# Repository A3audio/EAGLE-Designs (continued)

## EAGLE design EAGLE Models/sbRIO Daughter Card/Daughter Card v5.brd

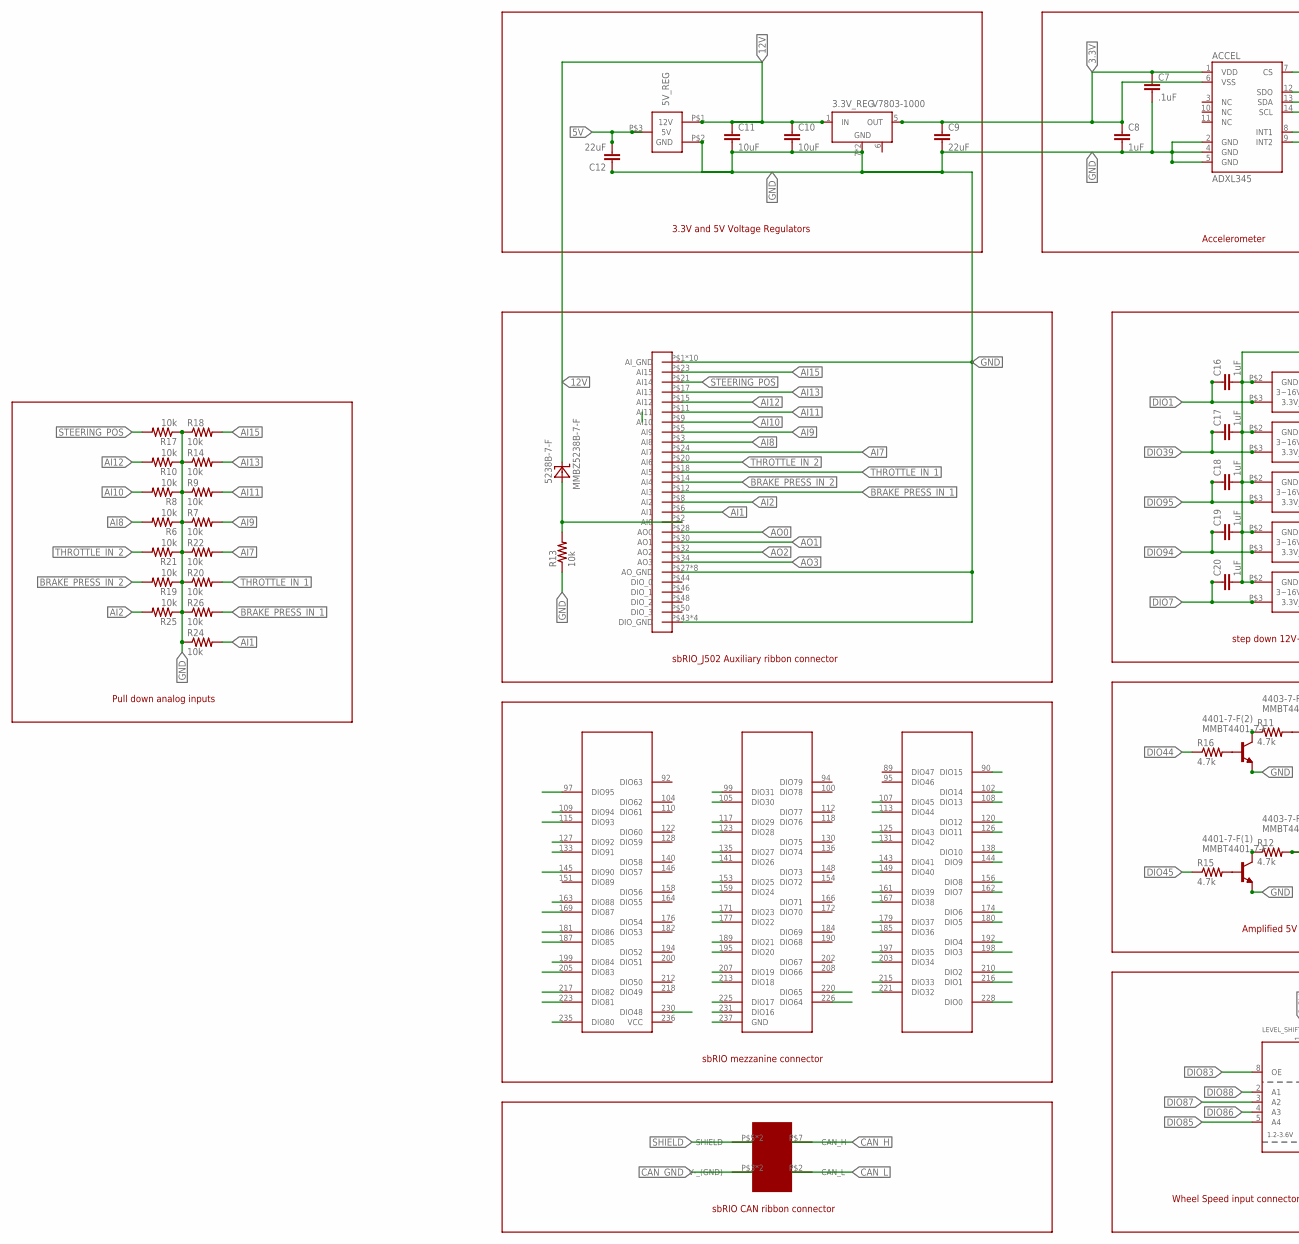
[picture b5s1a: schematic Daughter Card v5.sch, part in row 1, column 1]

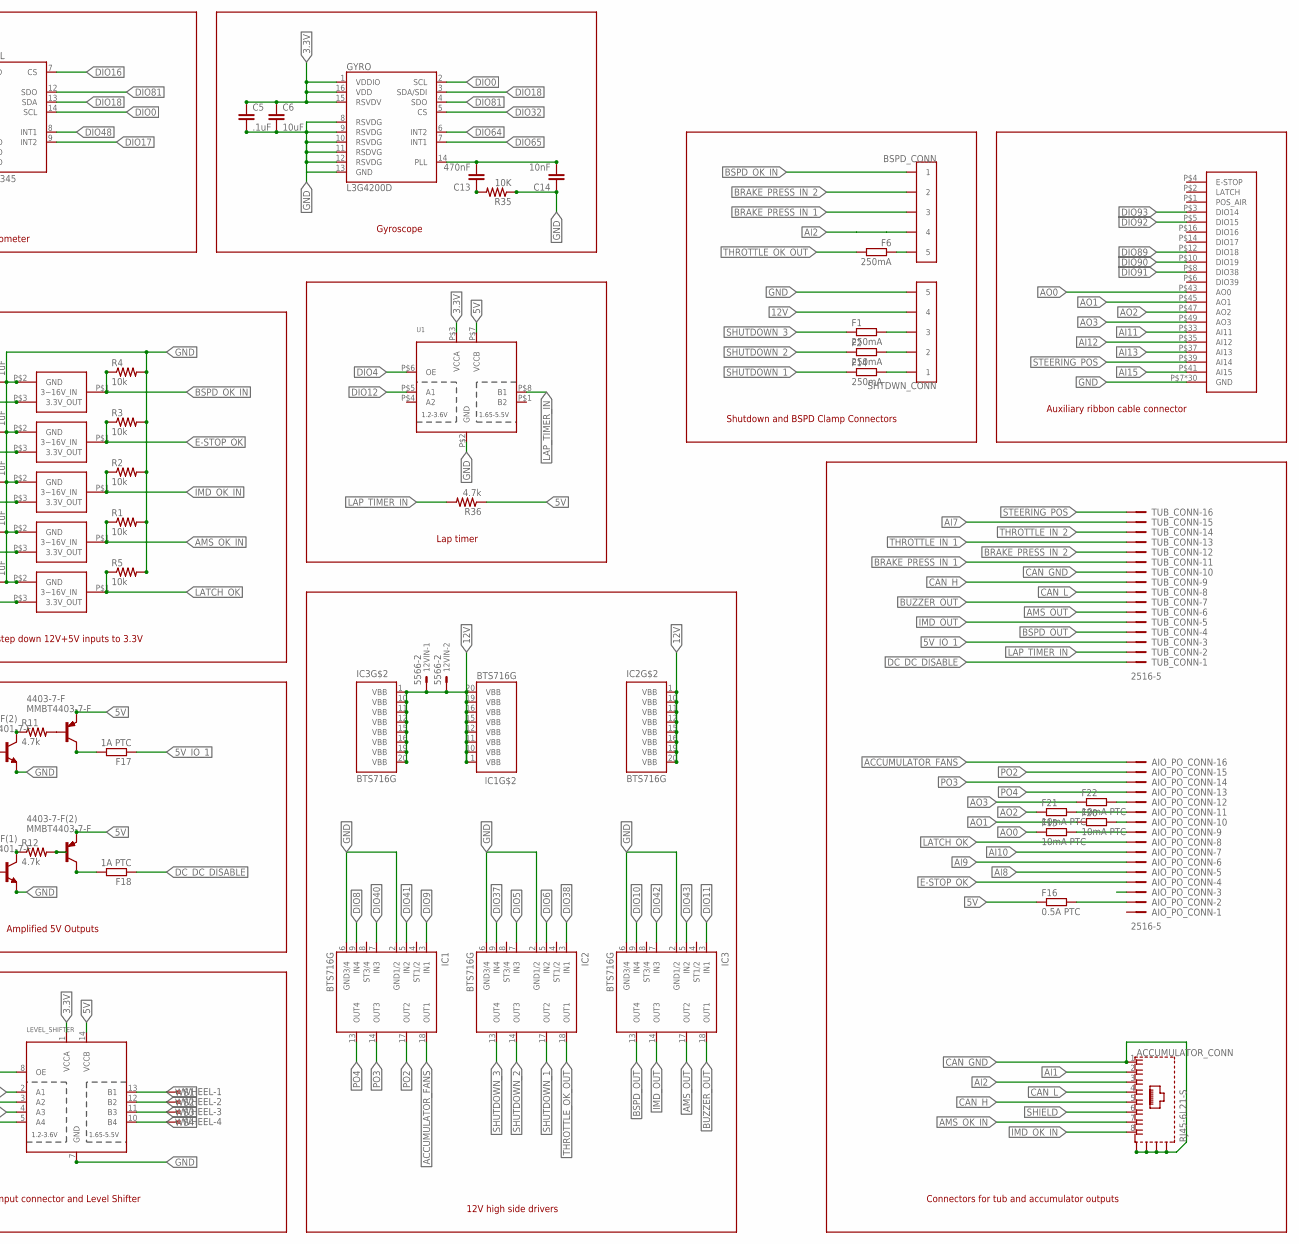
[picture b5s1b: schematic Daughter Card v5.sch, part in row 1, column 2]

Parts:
3.3V_REG: V7803-1000; V78XX-1000
5V_REG: V78XX-1500; V78XX-1500R
12VIN: 5566-2
4401-7-F(1), 4401-7-F(2): MMBT4401-7-F; SOT-23-3
4403-7-F, 4403-7-F(2): MMBT4403-7-F; SOT-23-3
5225-3.3M5-TR(5), 5525-3.3YM5-TR(1), 5525-3.3YM5-TR(2), 5525-3.3YM5-TR(3), 5525-3.3YM5-TR(4): MIC5225-3.3YM5-TR; SOT-23-3
5238B-7-F: MMBZ5238B-7-F; SOT-23-3
ACCEL: ADXL345; LGA14
ACCUMULATOR_CONN: RJ45-6L21-S; RJ45-SHIELD1
AIO_PO_CONN: 2516-5; PAK100/2500-5-16
BSPD_CONN: CONN_5; CONNECTOR_5
C5, C7: .1uF; 0603-CAP
C6, C10, C11: 10uF; 0603-CAP
C8, C16, C17, C18, C19, C20: 1uF; 0603-CAP
C9, C12: 22uF; 0603-CAP
C13: 470nF; 0603-CAP
C14: 10nF; 0603-CAP
F1, F2, F6, F14: 250mA; R0603
F15, F20, F21, F22: 10mA PTC; R0402
F16: 0.5A PTC; R0603
F17, F18: 1A PTC; R0603
GYRO: L3G4200D; LGA16-4X4
IC1, IC2, IC3: BTS716G; PG-DSO-20
LEVEL_SHIFTER: TXB0104PWR; TSSOP14
R1, R2, R3, R4, R5, R6, R7, R8, R9, R10, R13, R14, R17, R18, R19, R20, R21, R22, R24, R25, R26: 10k; R0402
R11, R12, R15, R16, R36: 4.7k; R0402
R35: 10K; 0603-RES
SBRIO_ANALOG: SBRIO_MIO; SBRIO_J502_J503
SBRIO_AUX: SBRIO_AUX; SBRIO_J502_J503
SBRIO_CAN: SBRIO_W500; SBRIO_W
SBRIO_MEZZANINE: SBRIO_RMC; SEAM-40-XX.X-XX-06-X-A
SHTDWN_CONN: CONN_5; CONNECTOR_5
TUB_CONN: 2516-5; PAK100/2500-5-16
U1: TXS0102; VFSOP-8
WHEEL: FTOP-4

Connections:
3.3V: 3.3V_REG.5 (OUT), ACCEL.1 (VDD), ACCEL.6 (VSS), C5.1, C6.1, C7.1, C8.1, C9.1, GYRO.1 (VDDIO), GYRO.15 (RSVDV), GYRO.16 (VDD), LEVEL_SHIFTER.1 (VCCA), U1.P$3 (VCCA)
5V: 5V_REG.P$3 (5V), 4403-7-F.P$3 (E), 4403-7-F(2).P$3 (E), C12.2, F16.1, LEVEL_SHIFTER.14 (VCCB), R36.1, U1.P$7 (VCCB)
5V_FUSED: AIO_PO_CONN.2, F16.2
5V_IO_1: F17.1, TUB_CONN.3
12V: 3.3V_REG.1 (IN), 5V_REG.P$1 (12V), 12VIN.1, 12VIN.2, 5238B-7-F.P$1 (C), C10.1, C11.1, IC1.1 (VBB), IC1.10 (VBB), IC1.11 (VBB), IC1.12 (VBB), IC1.15 (VBB), IC1.16 (VBB), IC1.19 (VBB), IC1.20 (VBB), IC2.1 (VBB), IC2.10 (VBB), IC2.11 (VBB), IC2.12 (VBB), IC2.15 (VBB), IC2.16 (VBB), IC2.19 (VBB), IC2.20 (VBB), IC3.1 (VBB), IC3.10 (VBB), IC3.11 (VBB), IC3.12 (VBB), IC3.15 (VBB), IC3.16 (VBB), IC3.19 (VBB), IC3.20 (VBB), SHTDWN_CONN.7 (4), SHTDWN_CONN.8 (4)
ACCUMULATOR_FANS: AIO_PO_CONN.16, IC1.18 (OUT1)
AI1: ACCUMULATOR_CONN.2, R24.2, SBRIO_ANALOG.P$6 (AI1)
AI2: ACCUMULATOR_CONN.3, BSPD_CONN.7 (4), BSPD_CONN.8 (4), R25.2, SBRIO_ANALOG.P$8 (AI2)
AI7: R22.2, SBRIO_ANALOG.P$24 (AI7), TUB_CONN.15
AI8: AIO_PO_CONN.5, R6.2, SBRIO_ANALOG.P$3 (AI8)
AI9: AIO_PO_CONN.6, R7.2, SBRIO_ANALOG.P$5 (AI9)
AI10: AIO_PO_CONN.7, R8.2, SBRIO_ANALOG.P$9 (AI10)
AI11: R9.2, SBRIO_ANALOG.P$11 (AI11), SBRIO_AUX.P$33 (AI11)
AI12: R10.2, SBRIO_ANALOG.P$15 (AI12), SBRIO_AUX.P$35 (AI12)
AI13: R14.2, SBRIO_ANALOG.P$17 (AI13), SBRIO_AUX.P$37 (AI13)
AI15: R18.2, SBRIO_ANALOG.P$23 (AI15), SBRIO_AUX.P$41 (AI15)
AMS_OK_IN: 5525-3.3YM5-TR(1).P$1 (3~16V_IN), ACCUMULATOR_CONN.7, R1.1
AMS_OUT: IC3.17 (OUT2), TUB_CONN.6
AO0: F15.1, SBRIO_ANALOG.P$28 (AO0), SBRIO_AUX.P$43 (AO0)
AO1: F20.1, SBRIO_ANALOG.P$30 (AO1), SBRIO_AUX.P$45 (AO1)
AO2: F21.1, SBRIO_ANALOG.P$32 (AO2), SBRIO_AUX.P$47 (AO2)
AO3: F22.1, SBRIO_ANALOG.P$34 (AO3), SBRIO_AUX.P$49 (AO3)
BRAKE_PRESS_IN_1: BSPD_CONN.5 (3), BSPD_CONN.6 (3), R26.2, SBRIO_ANALOG.P$12 (AI3), TUB_CONN.11
BRAKE_PRESS_IN_2: BSPD_CONN.3 (2), BSPD_CONN.4 (2), R19.2, SBRIO_ANALOG.P$14 (AI4), TUB_CONN.12
BSPD_OK_IN: 5525-3.3YM5-TR(3).P$1 (3~16V_IN), BSPD_CONN.1, BSPD_CONN.2 (1), R4.1
BSPD_OUT: IC3.13 (OUT4), TUB_CONN.4
BUZZER_OUT: IC3.18 (OUT1), TUB_CONN.7
CAN_GND: ACCUMULATOR_CONN.1, ACCUMULATOR_CONN.S1 (S), ACCUMULATOR_CONN.S2 (S), ACCUMULATOR_CONN.S3 (S), ACCUMULATOR_CONN.S4 (S), SBRIO_CAN.P$3 (V-_(GND)), SBRIO_CAN.P$6 (V-_(GND)), TUB_CONN.10
CAN_H: ACCUMULATOR_CONN.5, SBRIO_CAN.P$7 (CAN_H), TUB_CONN.9
CAN_L: ACCUMULATOR_CONN.4, SBRIO_CAN.P$2 (CAN_L), TUB_CONN.8
DC_DC_DISABLE: F18.1, TUB_CONN.1
DIO0: ACCEL.14 (SCL), GYRO.2 (SCL), SBRIO_MEZZANINE.228 (DIO0)
DIO1: 5525-3.3YM5-TR(3).P$3 (3.3V_OUT), C16.1, SBRIO_MEZZANINE.216 (DIO1)
DIO2: SBRIO_MEZZANINE.210 (DIO2)
DIO3: SBRIO_MEZZANINE.198 (DIO3)
DIO4: SBRIO_MEZZANINE.192 (DIO4), U1.P$6 (OE)
DIO5: IC2.7 (IN3), SBRIO_MEZZANINE.180 (DIO5)
DIO6: IC2.5 (IN2), SBRIO_MEZZANINE.174 (DIO6)
DIO7: 5525-3.3YM5-TR(2).P$3 (3.3V_OUT), C20.1, SBRIO_MEZZANINE.162 (DIO7)
DIO8: IC1.9 (IN4), SBRIO_MEZZANINE.156 (DIO8)
DIO9: IC1.3 (IN1), SBRIO_MEZZANINE.144 (DIO9)
DIO10: IC3.9 (IN4), SBRIO_MEZZANINE.138 (DIO10)
DIO11: IC3.3 (IN1), SBRIO_MEZZANINE.126 (DIO11)
DIO12: SBRIO_MEZZANINE.120 (DIO12), U1.P$5 (A1)
DIO13: SBRIO_MEZZANINE.108 (DIO13)
DIO14: SBRIO_MEZZANINE.102 (DIO14)
DIO15: SBRIO_MEZZANINE.90 (DIO15)
DIO16: ACCEL.7 (CS), SBRIO_MEZZANINE.231 (DIO16)
DIO17: ACCEL.9 (INT2), SBRIO_MEZZANINE.225 (DIO17)
DIO18: ACCEL.13 (SDA), GYRO.3 (SDA/SDI), SBRIO_MEZZANINE.213 (DIO18)
DIO19: SBRIO_MEZZANINE.207 (DIO19)
DIO20: SBRIO_MEZZANINE.195 (DIO20)
DIO21: SBRIO_MEZZANINE.189 (DIO21)
DIO22: SBRIO_MEZZANINE.177 (DIO22)
DIO23: SBRIO_MEZZANINE.171 (DIO23)
DIO24: SBRIO_MEZZANINE.159 (DIO24)
DIO25: SBRIO_MEZZANINE.153 (DIO25)
DIO26: SBRIO_MEZZANINE.141 (DIO26)
DIO27: SBRIO_MEZZANINE.135 (DIO27)
DIO28: SBRIO_MEZZANINE.123 (DIO28)
DIO29: SBRIO_MEZZANINE.117 (DIO29)
DIO30: SBRIO_MEZZANINE.105 (DIO30)
DIO31: SBRIO_MEZZANINE.99 (DIO31)
DIO32: GYRO.5 (CS), SBRIO_MEZZANINE.221 (DIO32)
DIO33: SBRIO_MEZZANINE.215 (DIO33)
DIO34: SBRIO_MEZZANINE.203 (DIO34)
DIO35: SBRIO_MEZZANINE.197 (DIO35)
DIO36: SBRIO_MEZZANINE.185 (DIO36)
DIO37: IC2.9 (IN4), SBRIO_MEZZANINE.179 (DIO37)
DIO38: IC2.3 (IN1), SBRIO_MEZZANINE.167 (DIO38)
DIO39: 5525-3.3YM5-TR(4).P$3 (3.3V_OUT), C17.1, SBRIO_MEZZANINE.161 (DIO39)
DIO40: IC1.7 (IN3), SBRIO_MEZZANINE.149 (DIO40)
DIO41: IC1.5 (IN2), SBRIO_MEZZANINE.143 (DIO41)
DIO42: IC3.7 (IN3), SBRIO_MEZZANINE.131 (DIO42)
DIO43: IC3.5 (IN2), SBRIO_MEZZANINE.125 (DIO43)
DIO44: R16.1, SBRIO_MEZZANINE.113 (DIO44)
DIO45: R15.1, SBRIO_MEZZANINE.107 (DIO45)
DIO48: ACCEL.8 (INT1), SBRIO_MEZZANINE.230 (DIO48)
DIO64: GYRO.6 (INT2), SBRIO_MEZZANINE.226 (DIO64)
DIO65: GYRO.7 (INT1), SBRIO_MEZZANINE.220 (DIO65)
DIO80: SBRIO_MEZZANINE.235 (DIO80)
DIO81: ACCEL.12 (SDO), GYRO.4 (SDO), SBRIO_MEZZANINE.223 (DIO81)
DIO82: SBRIO_MEZZANINE.217 (DIO82)
DIO83: LEVEL_SHIFTER.8 (OE), SBRIO_MEZZANINE.205 (DIO83)
DIO84: SBRIO_MEZZANINE.199 (DIO84)
DIO85: LEVEL_SHIFTER.5 (A4), SBRIO_MEZZANINE.187 (DIO85)
DIO86: LEVEL_SHIFTER.4 (A3), SBRIO_MEZZANINE.181 (DIO86)
DIO87: LEVEL_SHIFTER.3 (A2), SBRIO_MEZZANINE.169 (DIO87)
DIO88: LEVEL_SHIFTER.2 (A1), SBRIO_MEZZANINE.163 (DIO88)
DIO89: SBRIO_AUX.P$12 (DIO18)
DIO90: SBRIO_AUX.P$10 (DIO19), SBRIO_MEZZANINE.145 (DIO90)
DIO91: SBRIO_AUX.P$8 (DIO38), SBRIO_MEZZANINE.133 (DIO91)
DIO92: SBRIO_AUX.P$5 (DIO15), SBRIO_MEZZANINE.127 (DIO92)
DIO93: SBRIO_AUX.P$3 (DIO14), SBRIO_MEZZANINE.115 (DIO93)
DIO94: 5525-3.3YM5-TR(1).P$3 (3.3V_OUT), C19.1, SBRIO_MEZZANINE.109 (DIO94)
DIO95: 5225-3.3M5-TR(5).P$3 (3.3V_OUT), C18.1, SBRIO_MEZZANINE.97 (DIO95)
E-STOP_OK: 5525-3.3YM5-TR(4).P$1 (3~16V_IN), AIO_PO_CONN.4, R3.1
GND: 3.3V_REG.7 (GND), 3.3V_REG.9 (GND), 5V_REG.P$2 (GND), 4401-7-F(1).P$3 (E), 4401-7-F(2).P$3 (E), 5225-3.3M5-TR(5).P$2 (GND), 5525-3.3YM5-TR(1).P$2 (GND), 5525-3.3YM5-TR(2).P$2 (GND), 5525-3.3YM5-TR(3).P$2 (GND), 5525-3.3YM5-TR(4).P$2 (GND), ACCEL.2 (GND), ACCEL.4 (GND), ACCEL.5 (GND), C5.2, C6.2, C7.2, C8.2, C9.2, C10.2, C11.2, C12.1, C14.1, C16.2, C17.2, C18.2, C19.2, C20.2, GYRO.8 (RSVDG), GYRO.9 (RSVDG), GYRO.10 (RSVDG), GYRO.11 (RSDVG), GYRO.12 (RSVDG), GYRO.13 (GND), IC1.2 (GND1/2), IC1.6 (GND3/4), IC2.2 (GND1/2), IC2.6 (GND3/4), IC3.2 (GND1/2), IC3.6 (GND3/4), LEVEL_SHIFTER.7 (GND), R1.2, R2.2, R3.2, R4.2, R5.2, R6.1, R7.1, R8.1, R9.1, R10.1, R13.1, R14.1, R17.1, R18.1, R19.1, R20.1, R21.1, R22.1, R24.1, R25.1, R26.1, R35.1, SBRIO_ANALOG.P$1 (AI_GND), SBRIO_ANALOG.P$4 (AI_GND), SBRIO_ANALOG.P$7 (AI_GND), SBRIO_ANALOG.P$10 (AI_GND), SBRIO_ANALOG.P$13 (AI_GND), SBRIO_ANALOG.P$16 (AI_GND), SBRIO_ANALOG.P$19 (AI_GND), SBRIO_ANALOG.P$22 (AI_GND), SBRIO_ANALOG.P$25 (AI_GND), SBRIO_ANALOG.P$26 (AI_GND), SBRIO_ANALOG.P$27 (AO_GND), SBRIO_ANALOG.P$29 (AO_GND), SBRIO_ANALOG.P$31 (AO_GND), SBRIO_ANALOG.P$33 (AO_GND), SBRIO_ANALOG.P$35 (AO_GND), SBRIO_ANALOG.P$37 (AO_GND), SBRIO_ANALOG.P$39 (AO_GND), SBRIO_ANALOG.P$41 (AO_GND), SBRIO_ANALOG.P$43 (DIO_GND), SBRIO_ANALOG.P$45 (DIO_GND), SBRIO_ANALOG.P$47 (DIO_GND), SBRIO_ANALOG.P$49 (DIO_GND), SBRIO_AUX.P$7 (GND), SBRIO_AUX.P$9 (GND), SBRIO_AUX.P$11 (GND), SBRIO_AUX.P$13 (GND), SBRIO_AUX.P$15 (GND), SBRIO_AUX.P$17 (GND), SBRIO_AUX.P$18 (GND), SBRIO_AUX.P$19 (GND), SBRIO_AUX.P$20 (GND), SBRIO_AUX.P$21 (GND), SBRIO_AUX.P$22 (GND), SBRIO_AUX.P$23 (GND), SBRIO_AUX.P$24 (GND), SBRIO_AUX.P$25 (GND), SBRIO_AUX.P$26 (GND), SBRIO_AUX.P$27 (GND), SBRIO_AUX.P$28 (GND), SBRIO_AUX.P$29 (GND), SBRIO_AUX.P$30 (GND), SBRIO_AUX.P$31 (GND), SBRIO_AUX.P$32 (GND), SBRIO_AUX.P$34 (GND), SBRIO_AUX.P$36 (GND), SBRIO_AUX.P$38 (GND), SBRIO_AUX.P$40 (GND), SBRIO_AUX.P$42 (GND), SBRIO_AUX.P$44 (GND), SBRIO_AUX.P$46 (GND), SBRIO_AUX.P$48 (GND), SBRIO_AUX.P$50 (GND), SBRIO_MEZZANINE.237 (GND), SHTDWN_CONN.9 (5), SHTDWN_CONN.10 (5), U1.P$2 (GND)
IMD_OK_IN: 5225-3.3M5-TR(5).P$1 (3~16V_IN), ACCUMULATOR_CONN.8, R2.1
IMD_OUT: IC3.14 (OUT3), TUB_CONN.5
LAP_TIMER_IN: R36.2, TUB_CONN.2, U1.P$8 (B1)
LATCH_OK: 5525-3.3YM5-TR(2).P$1 (3~16V_IN), AIO_PO_CONN.8, R5.1
unnamed: AIO_PO_CONN.9, F15.2
unnamed: 5238B-7-F.P$2 (A), R13.2, SBRIO_ANALOG.P$2 (AI0)
unnamed: AIO_PO_CONN.10, F20.2
unnamed: AIO_PO_CONN.11, F21.2
unnamed: AIO_PO_CONN.12, F22.2
unnamed: F1.2, SHTDWN_CONN.5 (3), SHTDWN_CONN.6 (3)
unnamed: C13.2, C14.2, GYRO.14 (PLL)
unnamed: C13.1, R35.2
unnamed: BSPD_CONN.9 (5), BSPD_CONN.10 (5), F6.1
unnamed: 4403-7-F.P$2 (B), R11.2
unnamed: 4403-7-F.P$1 (C), F17.2
unnamed: 4403-7-F(2).P$1 (C), F18.2
unnamed: 4403-7-F(2).P$2 (B), R12.2
unnamed: 4401-7-F(1).P$2 (B), R15.2
unnamed: 4401-7-F(1).P$1 (C), R12.1
unnamed: 4401-7-F(2).P$2 (B), R16.2
unnamed: 4401-7-F(2).P$1 (C), R11.1
PO2: AIO_PO_CONN.15, IC1.17 (OUT2)
PO3: AIO_PO_CONN.14, IC1.14 (OUT3)
PO4: AIO_PO_CONN.13, IC1.13 (OUT4)
SHIELD: ACCUMULATOR_CONN.6, SBRIO_CAN.P$5 (SHIELD), SBRIO_CAN.P$10 (SHIELD)
SHUTDOWN_1: F14.1, IC2.17 (OUT2)
SHUTDOWN_1_FUSED: F14.2, SHTDWN_CONN.1, SHTDWN_CONN.2 (1)
SHUTDOWN_2: F2.1, IC2.14 (OUT3)
SHUTDOWN_2_FUSED: F2.2, SHTDWN_CONN.3 (2), SHTDWN_CONN.4 (2)
SHUTDOWN_3: F1.1, IC2.13 (OUT4)
STEERING_POS: R17.2, SBRIO_ANALOG.P$21 (AI14), SBRIO_AUX.P$39 (AI14), TUB_CONN.16
THROTTLE_IN_1: R20.2, SBRIO_ANALOG.P$18 (AI5), TUB_CONN.13
THROTTLE_IN_2: R21.2, SBRIO_ANALOG.P$20 (AI6), TUB_CONN.14
THROTTLE_OK_OUT: F6.2, IC2.18 (OUT1)
VCC: SBRIO_MEZZANINE.236 (VCC)
WS1: LEVEL_SHIFTER.13 (B1), WHEEL.1
WS2: LEVEL_SHIFTER.12 (B2), WHEEL.2
WS3: LEVEL_SHIFTER.11 (B3), WHEEL.3
WS4: LEVEL_SHIFTER.10 (B4), WHEEL.4

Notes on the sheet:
step down 12V+5V inputs to 3.3V
Auxiliary ribbon cable connector
Amplified 5V Outputs
sbRIO CAN ribbon connector
sbRIO mezzanine connector
sbRIO_J502 Auxiliary ribbon connector
Gyroscope
3.3V and 5V Voltage Regulators
Accelerometer
Wheel Speed input connector and Level Shifter
Shutdown and BSPD Clamp Connectors
12V high side drivers
Lap timer
Connectors for tub and accumulator outputs
Pull down analog inputs

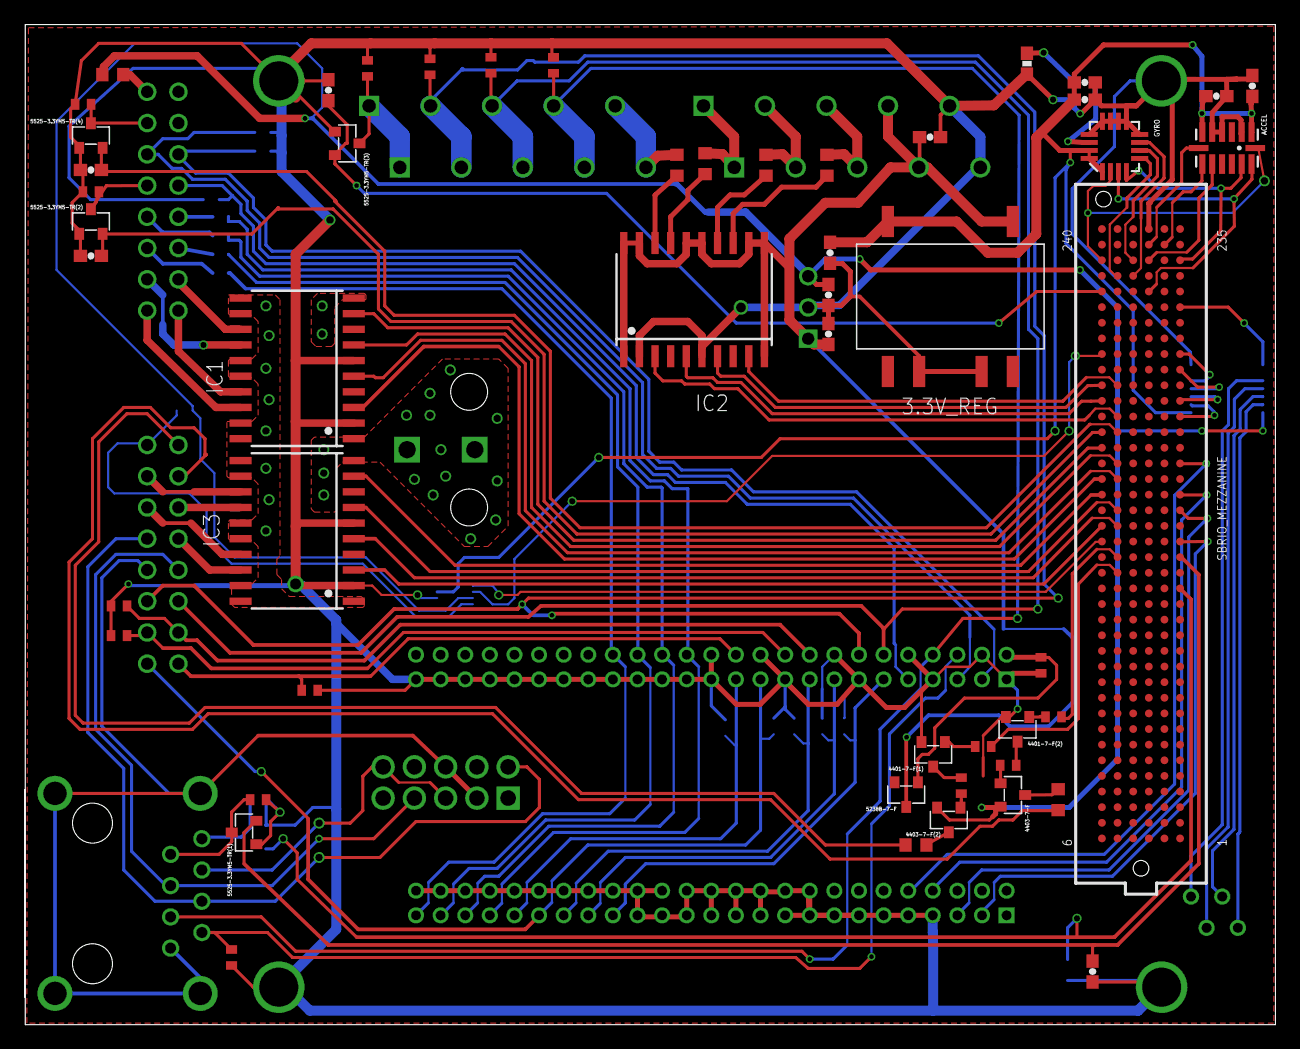
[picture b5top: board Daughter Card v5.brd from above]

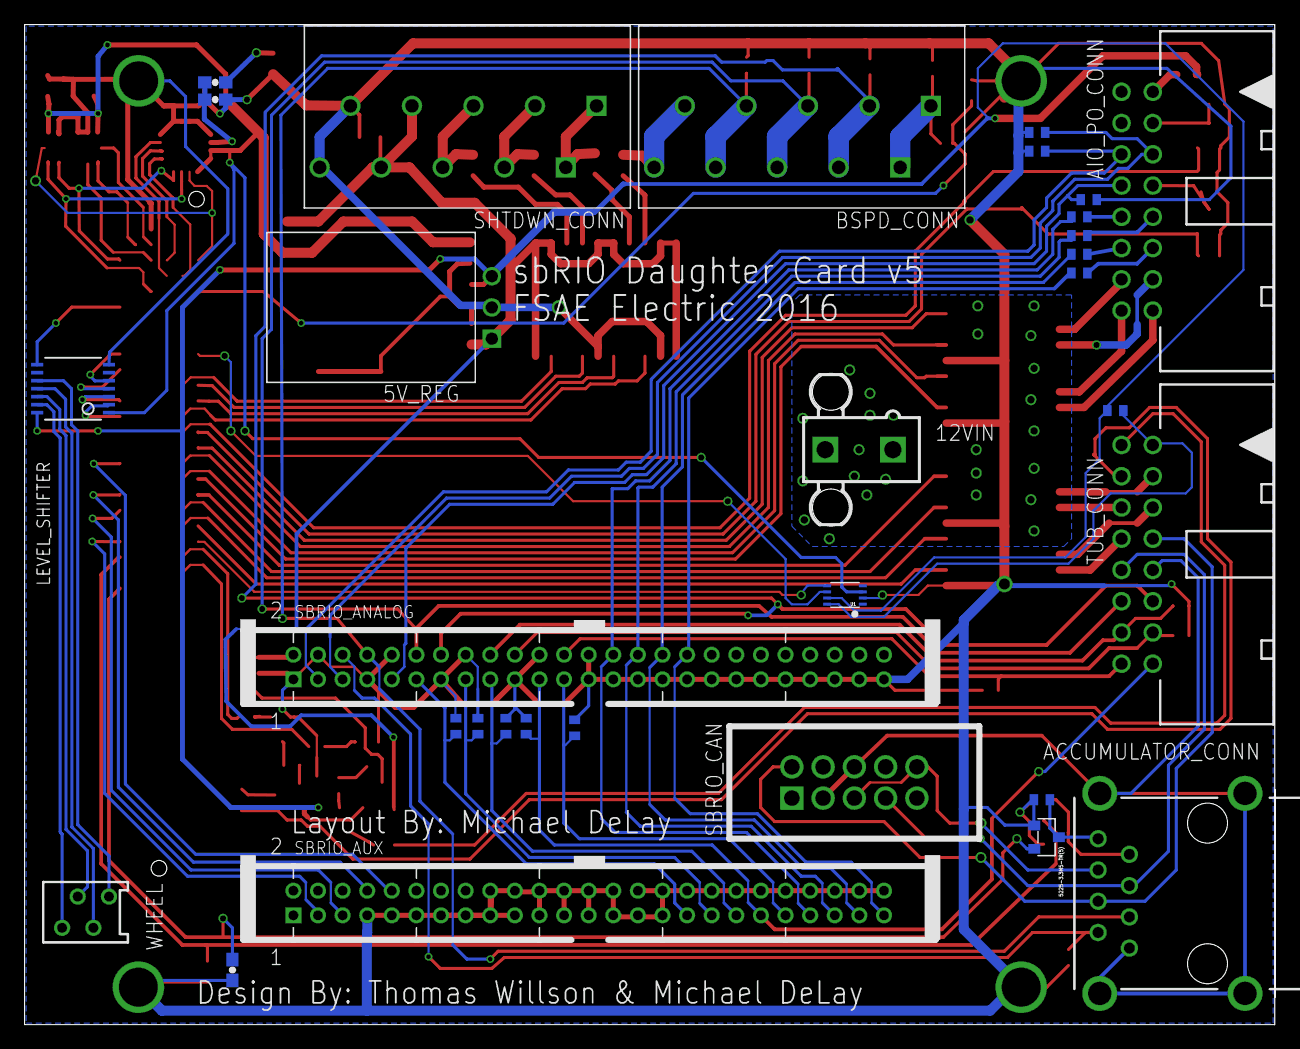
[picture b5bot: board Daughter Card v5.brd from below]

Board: 2 copper layers, 101.6 x 81.3 mm, 83 parts (31 on the bottom side), 110 nets.
